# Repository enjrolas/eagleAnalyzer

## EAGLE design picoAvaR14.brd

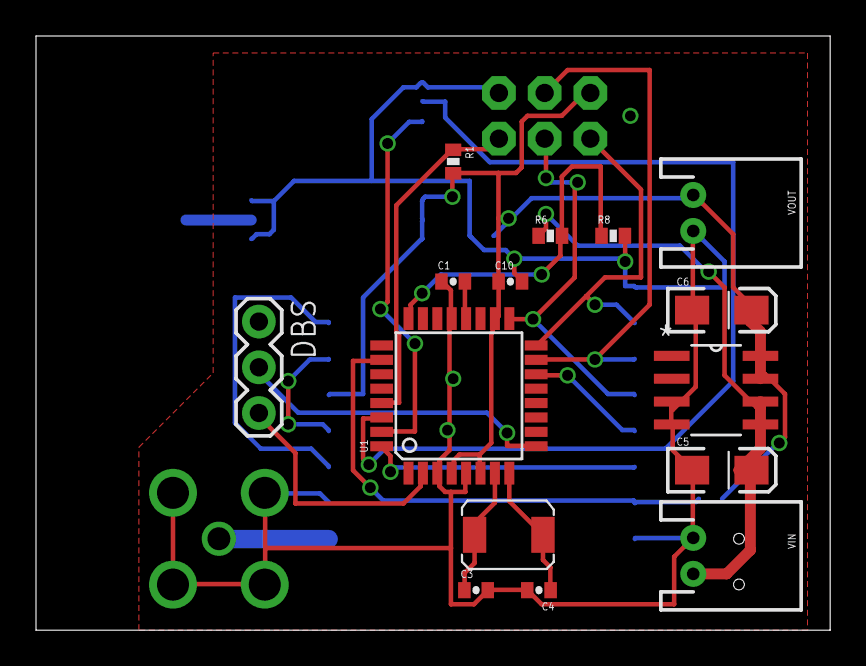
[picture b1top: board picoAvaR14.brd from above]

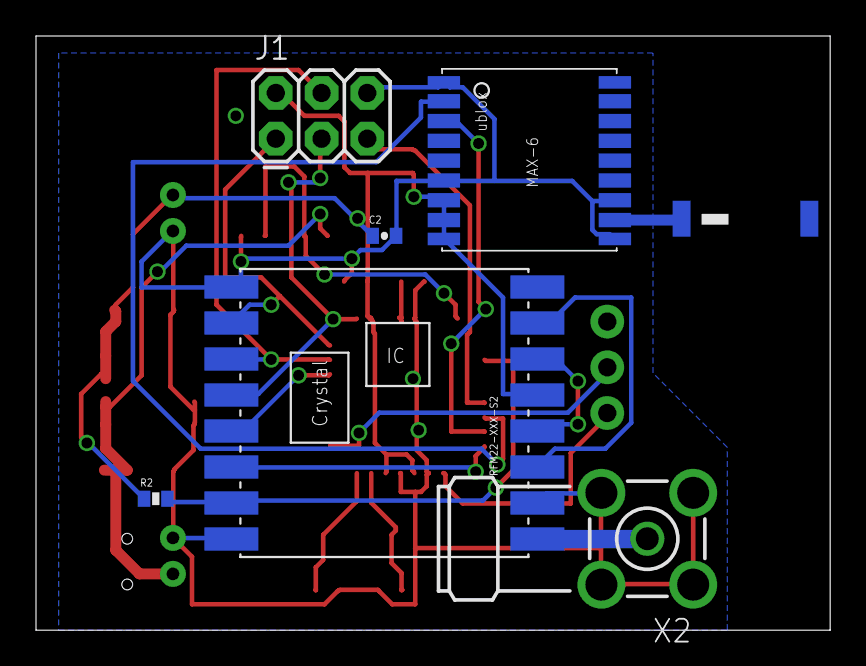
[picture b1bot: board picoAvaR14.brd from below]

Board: 2 copper layers, 44.1 x 33.0 mm, 24 parts (7 on the bottom side), 22 nets.

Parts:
C1, C2, C10: 0.1uF; 0402-CAP
C3, C4: 18pF; 0402-CAP
C5: EIA3216-KIT
C6: 4.7uF; EIA3216-KIT
DBS: 1X03
J1: AVR_SPI_PRG_6PTH; 2X3
JP1, JP2: STAND-OFF
R1, R2, R8: 10k; 0402-RES
R6: 100k; 0402-RES
RFM22-XXX-S2: RFM22; RFM22-XXX-S2
U1: ATMEGA328; TQFP32-08
U2: TPS76633D; SOIC127P600X175-8N
U$1: UBLOX_MAX-6
U$2: ABRACON_ABM3_CRYSTAL
U$3: JTI_ANTENNA-1575AT43A40
VIN: JST-2-PTH
VOUT: JST-2-PTH
X2: BU-SMA-H

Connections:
AREF: C1.2, U1.20
GND: C1.1, C2.2, C3.2, C4.2, C5.C, C6.C, C10.2, DBS.1, J1.6, R8.2, RFM22-XXX-S2.2, RFM22-XXX-S2.9, RFM22-XXX-S2.16, U1.3, U1.5, U1.21, U2.3, U2.4, U$1.1_GND, U$1.6_V_BCKP, U$1.10_GND, U$1.12_GND, VIN.1, VOUT.2, X2.2, X2.3, X2.4, X2.5
MISO: J1.1, RFM22-XXX-S2.10, U1.16
MOSI: J1.4, RFM22-XXX-S2.11, U1.15
unnamed: RFM22-XXX-S2.1, X2.1
unnamed: U$1.11_RF_IN, U$3.FEED
unnamed: RFM22-XXX-S2.3, RFM22-XXX-S2.7
unnamed: RFM22-XXX-S2.4, RFM22-XXX-S2.6
unnamed: C3.1, U1.7, U$2.P$2
unnamed: C4.1, U1.8, U$2.P$1
NSS_RX: DBS.2, U1.9
NSS_TX: DBS.3, U1.2
RESET: J1.5, R1.1, U1.29
RFM22_NIRQ: RFM22-XXX-S2.14, U1.32
RFM22_NSEL: RFM22-XXX-S2.13, U1.14
RFM22_SDN: R2.2, RFM22-XXX-S2.15, U1.26
SCK: J1.3, RFM22-XXX-S2.12, U1.17
UBLOX_RXD: U1.31, U$1.3_RXD1
UBLOX_TXD: U1.30, U$1.2_TXD1
VBATT: C5.A, R6.1, U2.5, U2.6, VIN.2
VBATTADC: R6.2, R8.1, U1.24
VCC: C2.1, C6.A, C10.1, J1.2, R1.2, R2.1, RFM22-XXX-S2.5, U1.4, U1.6, U1.18, U2.7, U2.8, U$1.7_VCC_IO, U$1.8_VCC, U$1.9_V_RESET, VOUT.1

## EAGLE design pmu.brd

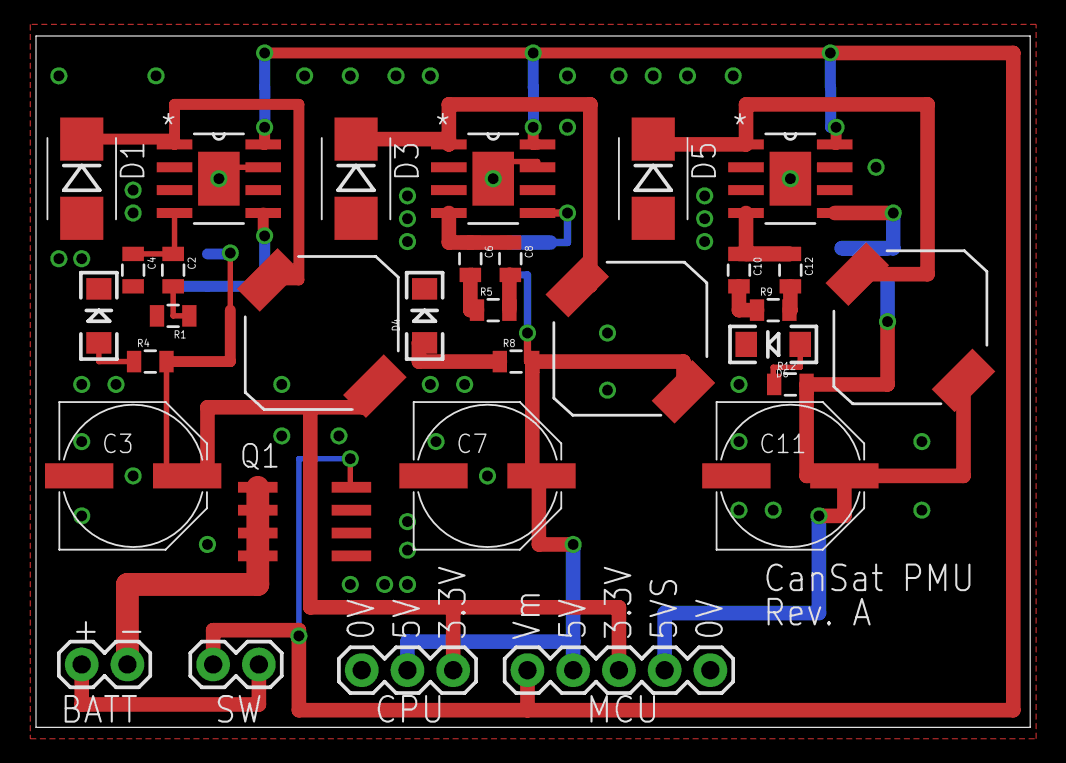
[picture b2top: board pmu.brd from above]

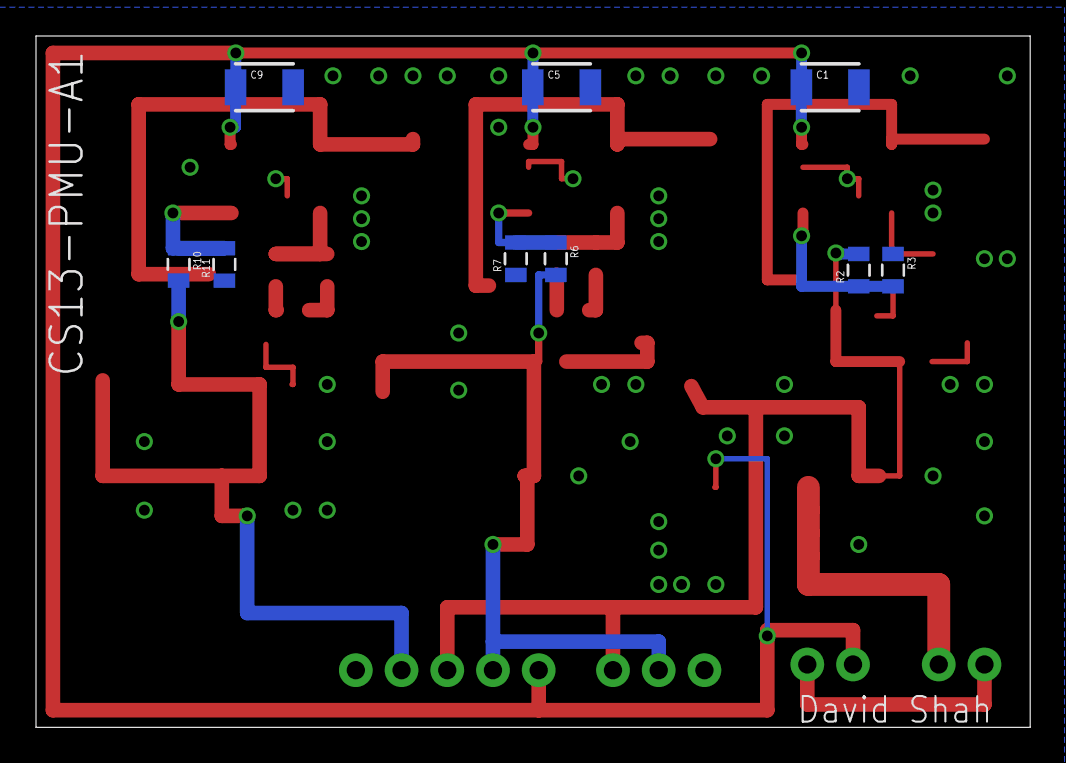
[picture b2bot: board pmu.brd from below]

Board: 2 copper layers, 55.2 x 38.4 mm, 41 parts (9 on the bottom side), 22 nets.

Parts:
BATT: 1X02
C1, C5, C9: 10u; 1210
C2, C6, C10: 22n; 0805
C3, C7, C11: 330u; PANASONIC_E
C4, C8, C12: 220p; 0805
CPU_PWR: 1X03
D1, D3, D5: SMB-DIODE
D2, D4, D6: GREEN; LED-1206
L1, L2, L3: 15uH; IND_ELL8TP
MCU_PWR: 1X05
PSW: 1X02
Q1: SO-08
R1, R5, R9: 4k7; 0805
R2: 5.6k; 0805
R3: 3.3k; 0805
R4, R8, R12: 330; 0805
R6, R10: 8.2k; 0805
R7, R11: 2.7k; 0805
U1, U2, U3: L5973D; SOP127P600X170-9N

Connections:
3.3V: C3.+, CPU_PWR.3, L1.1, MCU_PWR.3, R2.2, R4.2
5V: C7.+, CPU_PWR.2, L2.1, MCU_PWR.4, R6.2, R8.2
5VS: C11.+, L3.1, MCU_PWR.2, R10.2, R12.2
GND: C1.2, C3.-, C4.2, C5.2, C7.-, C8.2, C9.2, C11.-, C12.2, CPU_PWR.1, D1.A, D2.C, D3.A, D4.C, D5.A, D6.C, MCU_PWR.1, Q1.1, Q1.2, Q1.3, R1.2, R3.1, R5.2, R7.1, R9.2, R11.1, U1.3, U1.7, U1.9, U2.3, U2.7, U2.9, U3.3, U3.7, U3.9
unnamed: C2.1, C4.1, U1.4
unnamed: C2.2, R1.1
unnamed: D1.C, L1.2, U1.1
unnamed: BATT.2, Q1.5, Q1.6, Q1.7, Q1.8
unnamed: R2.1, R3.2, U1.5
unnamed: D2.A, R4.1
unnamed: C10.1, C12.1, U3.4
unnamed: C6.1, C8.1, U2.4
unnamed: C6.2, R5.1
unnamed: D3.C, L2.2, U2.1
unnamed: R6.1, R7.2, U2.5
unnamed: D4.A, R8.1
unnamed: C10.2, R9.1
unnamed: D5.C, L3.2, U3.1
unnamed: R10.1, R11.2, U3.5
unnamed: D6.A, R12.1
unnamed: BATT.1, PSW.2
V_BATT: C1.1, C5.1, C9.1, MCU_PWR.5, PSW.1, Q1.4, U1.8, U2.8, U3.8

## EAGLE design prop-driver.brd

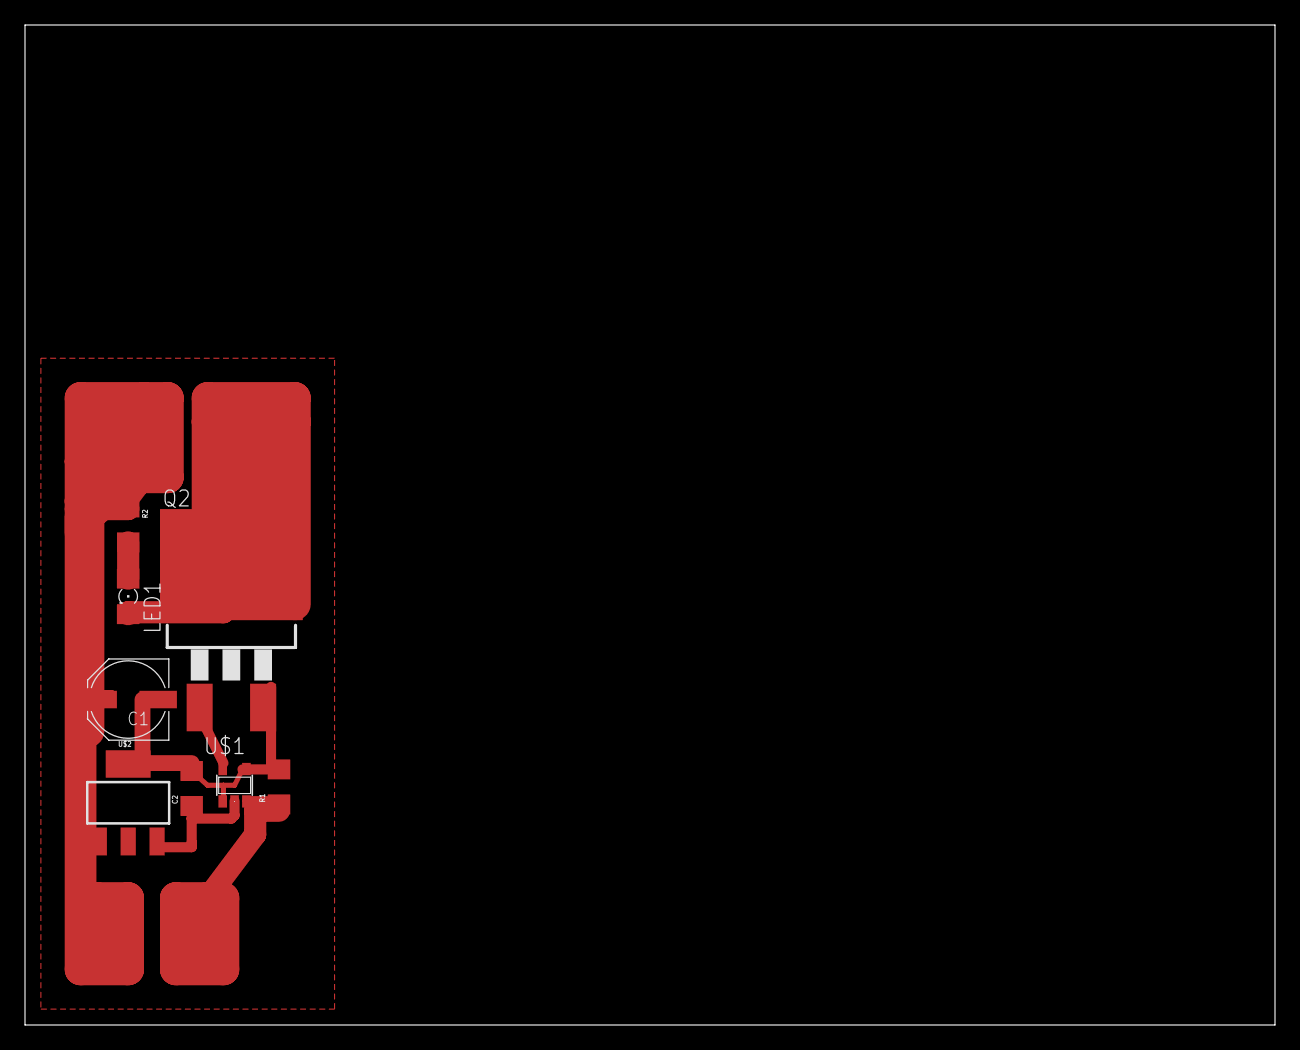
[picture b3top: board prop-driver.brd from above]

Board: 2 copper layers, 100.0 x 80.0 mm, 8 parts (0 on the bottom side), 7 nets.

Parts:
C1: PANASONIC_D
C2: 1206
LED1: FKIT-LED-1206
Q2: IRF3704S; D2PACK
R1, R2: 1206
U$1: MCP1402; SOT23-5
U$2: V_REG_MIC2920; SOT223

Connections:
+5V: C2.1, U$1.2, U$2.3
GND: C1.-, C2.2, Q2.3, R1.2, U$1.1, U$1.4, U$2.2
unnamed: Q2.1, U$1.5
unnamed: R1.1, U$1.3
unnamed: LED1.C, Q2.2
unnamed: LED1.A, R2.2
VDD: C1.+, R2.1, U$2.1

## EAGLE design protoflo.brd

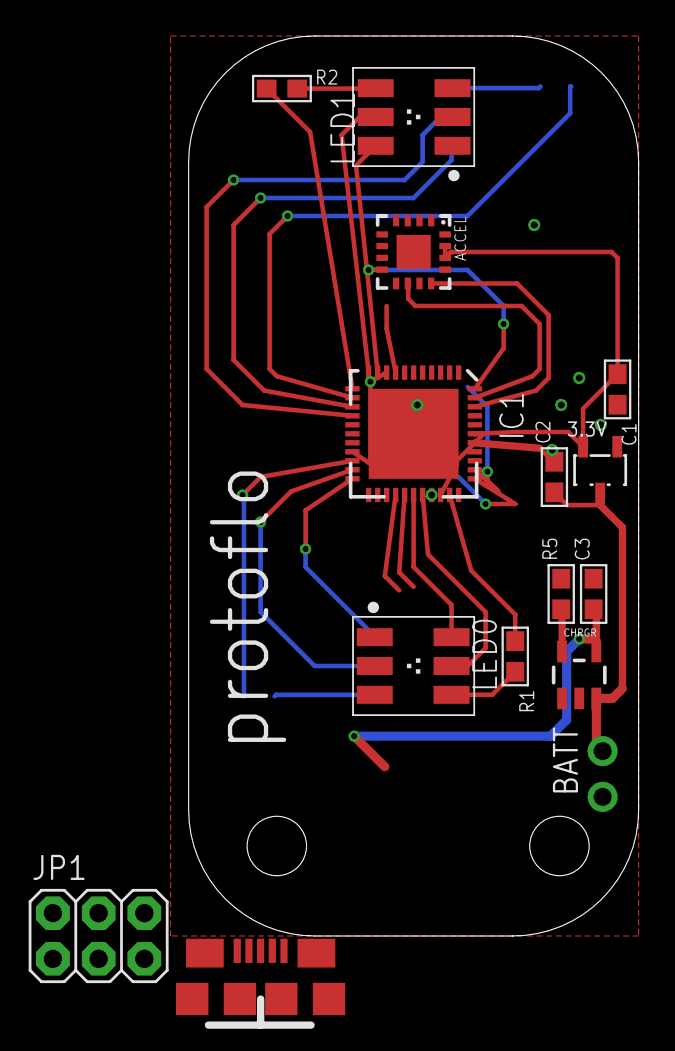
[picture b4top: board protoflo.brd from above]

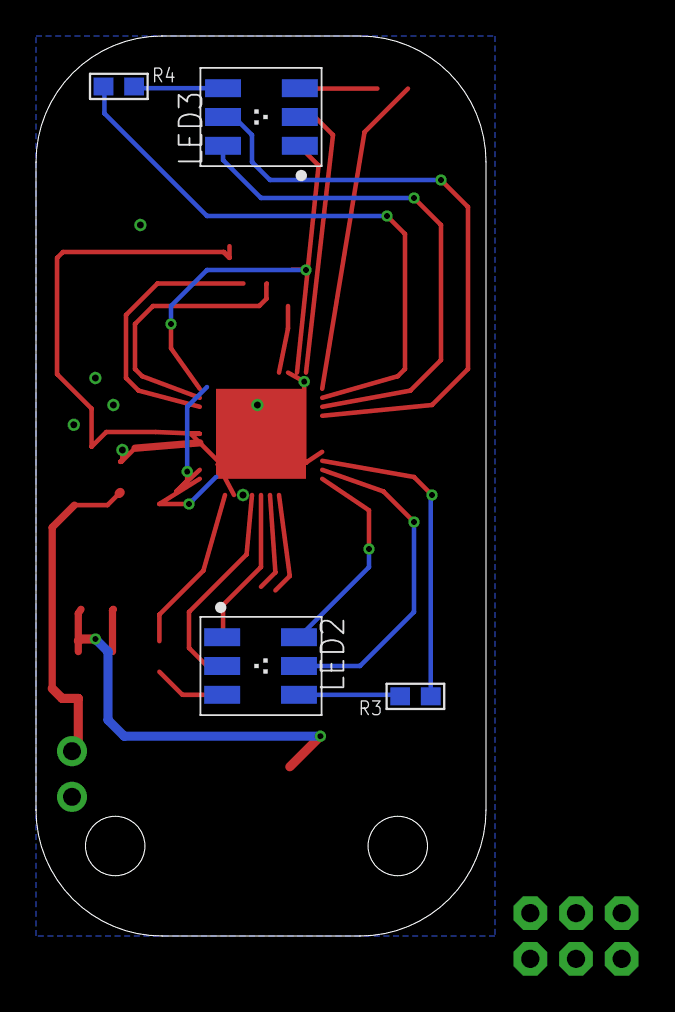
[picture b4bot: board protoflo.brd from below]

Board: 2 copper layers, 25.0 x 50.0 mm, 21 parts (4 on the bottom side), 28 nets.

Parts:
3.3V: VREG; SOT23-3
ACCEL: LFCSP-16
BATT: 1X02_ROUND
C1: .1uF; 0603
C2: 1uF; 0603
C3: 4.7uF; 0603
CHRGR: MCP73831; SOT23-5
CN1: USB-MICROB
IC1: QFN-44
JP1: 2X03
LED0, LED1, LED2, LED3: RGBLED_PLCC6
R1, R2, R3, R4, R5: 0603
U$1, U$2: STAND-OFF

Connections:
3.3V: 3.3V.2, ACCEL.14, ACCEL.15, C1.1, IC1.9, IC1.19, IC1.31, IC1.39, JP1.2
5V: 3.3V.3, C3.1, CHRGR.4, CN1.P1
ACCEL-X: ACCEL.12, IC1.42
ACCEL-Y: ACCEL.10, IC1.43
ACCEL-Z: ACCEL.8, IC1.44
BATT: BATT.2, C2.1, CHRGR.3
D+: CN1.P3, IC1.27
D-: CN1.P2, IC1.26
GND: 3.3V.1, ACCEL.3, ACCEL.5, ACCEL.6, ACCEL.7, BATT.1, C1.2, C2.2, C3.2, CHRGR.2, CN1.P5, IC1.8, IC1.18, IC1.30, IC1.38, JP1.6, LED0.1, LED0.2, LED0.3, LED1.1, LED1.2, LED1.3, LED2.1, LED2.2, LED2.3, LED3.1, LED3.2, LED3.3, R5.2
LED0B: IC1.28, LED0.6
LED0G: IC1.29, LED0.5
LED0R: LED0.4, R1.2
LED0RR: IC1.32, R1.1
LED1B: IC1.10, LED1.6
LED1G: IC1.11, LED1.5
LED1R: LED1.4, R2.2
LED1RR: IC1.12, R2.1
LED2B: IC1.22, LED2.6
LED2G: IC1.21, LED2.5
LED2R: LED2.4, R3.2
LED2RR: IC1.20, R3.1
LED3B: IC1.14, LED3.6
LED3G: IC1.15, LED3.5
LED3R: LED3.4, R4.2
LED3RR: IC1.13, R4.1
unnamed: CHRGR.5, R5.1
PDI-CLK: IC1.35, JP1.5
PDI-DATA: IC1.34, JP1.1

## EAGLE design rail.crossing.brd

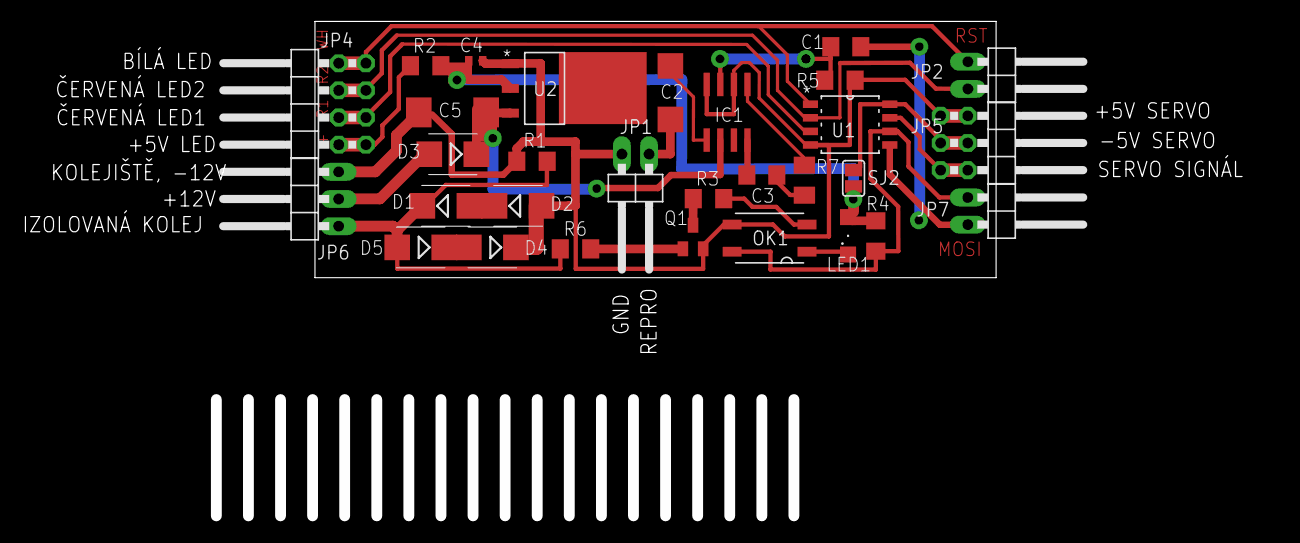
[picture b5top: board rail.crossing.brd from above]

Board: 2 copper layers, 63.7 x 24.0 mm, 30 parts (0 on the bottom side), 25 nets.

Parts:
C1: 100nF; C1206
C2: 100uF; SMC_C
C3: 10uF; C1206
C4: 1uF; C0402
C5: SMC_D
D1, D2, D3, D4, D5: M1; SMB
IC1: LM386M-1; SO08
JP1, JP2, JP7: 1X02/90
JP4: 2X04/90
JP5: 2X03/90
JP6: 1X03/90
LED1: KPT-3216SRD-PRV; SML1206
OK1: PC357N14; SMD4
Q1: BC847SMD; SOT23
R1: 2k2; R1206
R2, R3: 220; R1206
R4, R5: 10K; R1206
R6: 1K; R1206
R7: 1K; M1206
SJ2: SJ
U1: ATTINY85V-10SU; SOIC127P798X216-8N
U2: LM1117MP-5.0; SOT230P696X180-4N

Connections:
220: LED1.C, OK1.1
JP1: D3.C, D5.A, JP6.1, R1.1, R6.1
JP2: C4.2, D2.A, D4.C, IC1.2, IC1.4, JP1.2, JP5.1, JP5.2, JP6.3, OK1.3, Q1.2, R1.2, R5.2, U1.4, U2.1
unnamed: C2.-, JP1.1
unnamed: C3.1, R7.1
unnamed: C3.2, IC1.8
unnamed: D2.C, D3.A
unnamed: D4.A, D5.C
unnamed: Q1.1, R6.2
unnamed: Q1.3, R3.1
unnamed: C2.+, IC1.5
unnamed: OK1.2, R3.2
unnamed: JP5.5, JP5.6, U1.7
unnamed: C1.1, JP7.2, U1.5
unnamed: JP4.1, JP4.2, R2.1
unnamed: JP7.1, OK1.4, R4.1, U1.6
unnamed: JP5.3, JP5.4, LED1.A, R2.2, R4.2, SJ2.2, U1.8
unnamed: IC1.1, R7.2
unnamed: C1.2, IC1.3, R5.1
unnamed: C4.1, SJ2.1, U2.2
unnamed: D1.A, JP6.2
unnamed: C5.+, D1.C, IC1.6, U2.3
RED1: JP2.2, JP4.5, JP4.6, U1.2
RED2: JP4.3, JP4.4, U1.3
WHITE: JP2.1, JP4.7, JP4.8, U1.1

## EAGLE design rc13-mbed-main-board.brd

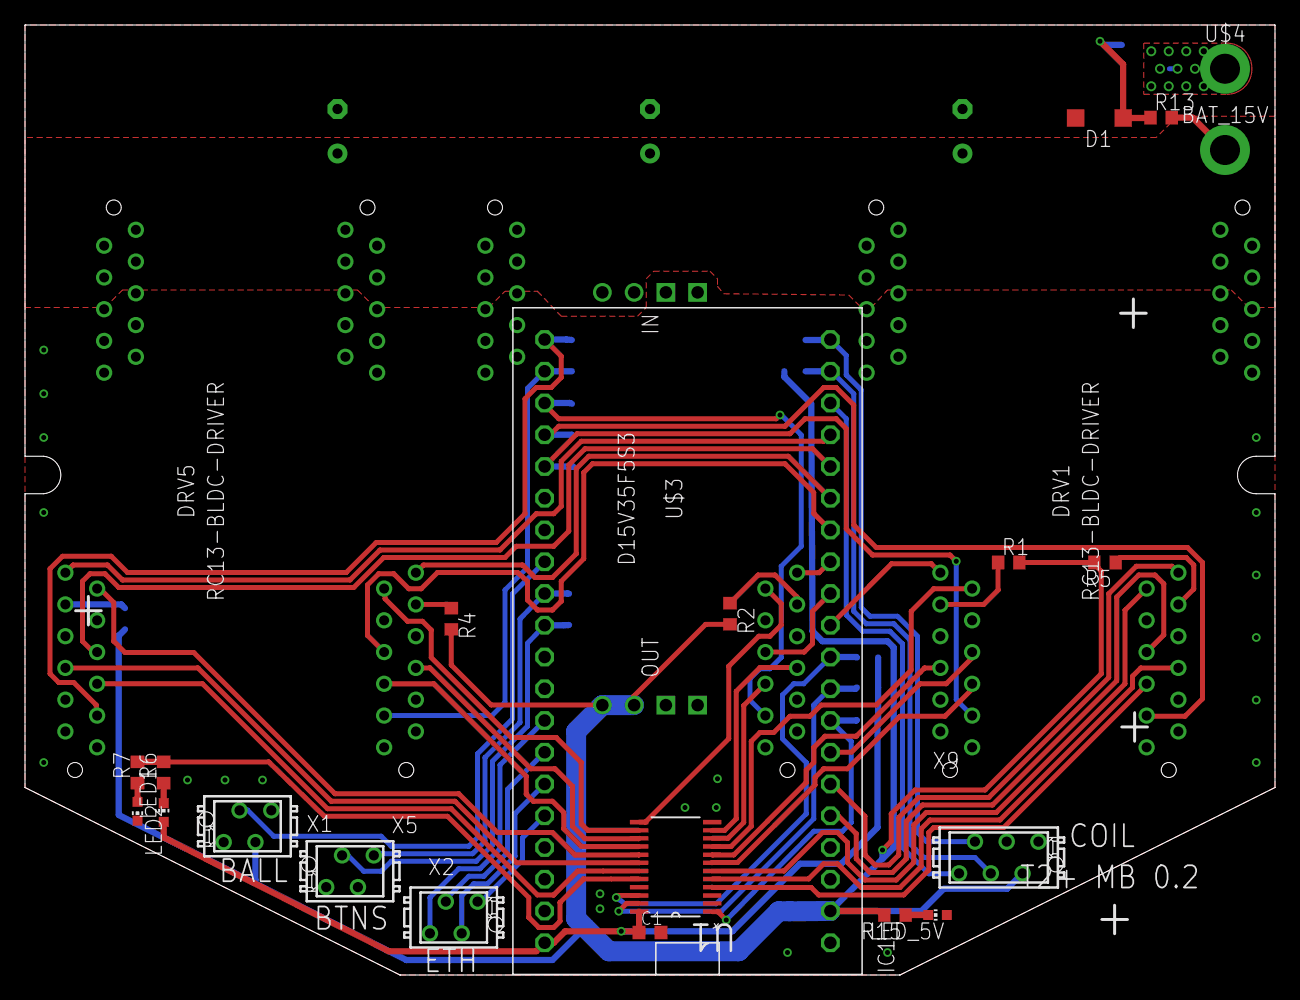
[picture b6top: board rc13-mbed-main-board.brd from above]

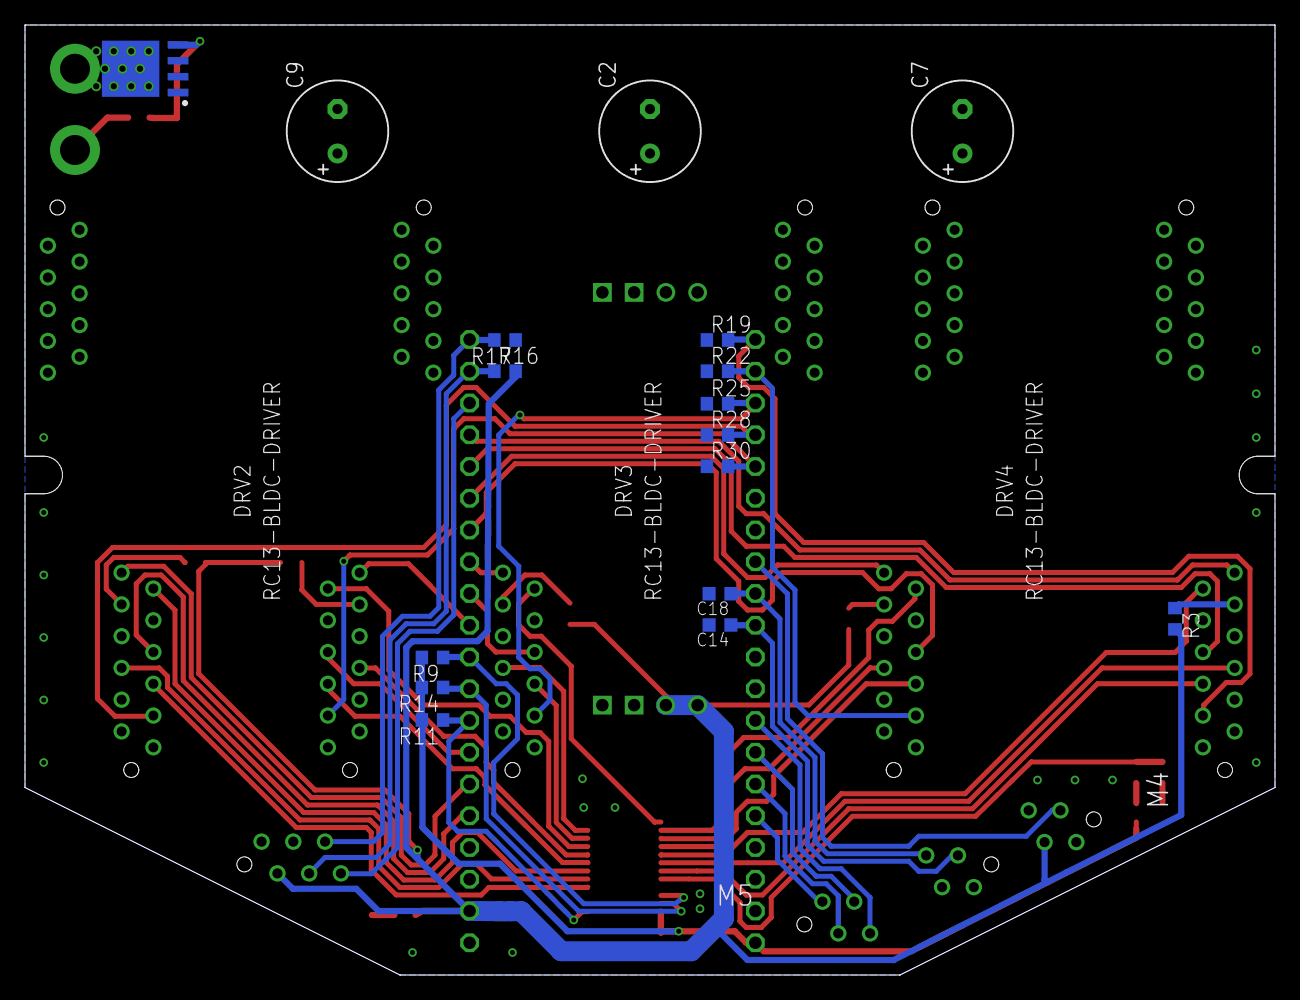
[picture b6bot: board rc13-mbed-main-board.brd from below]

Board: 2 copper layers, 100.0 x 76.0 mm, 44 parts (20 on the bottom side), 58 nets.

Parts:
BAT_15V: M01_PWR; PWR_HOLE
C1, C14, C18: 100nF; C0603K
C2, C7, C9: 470uF; E3,5-8
D1: 12V; SOD123
DRV1, DRV2, DRV3, DRV4, DRV5: RC13-BLDC-DRIVER
IC1: MBED_MICROCONTROLLER; DIL40_0.9
LED1, LED2: CHIP-LED0603
LED_5V: CHIP-LED0603
R1, R2, R3, R4, R5, R16, R17, R19, R22, R25, R28, R30: 10k; R0603
R6, R7, R9, R11, R14, R15: 2K2; R0603
R13: 100k; R0603
U1: PCA9555PW,118; SOP65P640X110-24N
U$2: MOSFET-N; TO127P600X120-5N
U$3: D15V35F5S3
U$4: M01_PWR; PWR_HOLE
X1: BALL_SENS; MICROMATCH-4
X2: ETH; MICROMATCH-4
X5: BTNS; MICROMATCH-4
X9: COIL; MICROMATCH-6

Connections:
+3V3: C1.1, IC1.40, LED1.A, R9.2, R11.2, R14.2, U1.24
+5V: IC1.2, R1.2, R2.2, R3.2, R4.2, R5.2, R15.2, R16.2, U$3.P$7, U$3.P$8, X1.3, X9.2
+15V: BAT_15V.P$1, C2.+, C7.+, C9.+, DRV1.PWR1, DRV1.PWR2, DRV1.PWR3, DRV1.PWR4, DRV1.PWR5, DRV2.PWR1, DRV2.PWR2, DRV2.PWR3, DRV2.PWR4, DRV2.PWR5, DRV3.PWR1, DRV3.PWR2, DRV3.PWR3, DRV3.PWR4, DRV3.PWR5, DRV4.PWR1, DRV4.PWR2, DRV4.PWR3, DRV4.PWR4, DRV4.PWR5, DRV5.PWR1, DRV5.PWR2, DRV5.PWR3, DRV5.PWR4, DRV5.PWR5, R13.2, U$3.EN, U$3.P$5
BALL: IC1.28, X1.2
BAT_GND: U$2.5, U$4.P$1
BRAKE1: DRV1.LOGIC6, U1.8
BRAKE2: DRV2.LOGIC6, U1.5
BRAKE3: DRV3.LOGIC6, U1.11
BRAKE4: DRV4.LOGIC6, U1.15
BRAKE5: DRV5.LOGIC6, U1.18
BTN1: C14.1, IC1.30, X5.2
BTN2: C18.1, IC1.29, X5.4
CHARGE: IC1.20, R17.2, X9.5
COAST1: DRV1.LOGIC11, U1.9
COAST2: DRV2.LOGIC11, U1.6
COAST3: DRV3.LOGIC11, U1.13
COAST4: DRV4.LOGIC11, U1.14
COAST5: DRV5.LOGIC11, U1.17
DIR1: DRV1.LOGIC5, U1.7
DIR2: DRV2.LOGIC5, U1.4
DIR3: DRV3.LOGIC5, U1.10
DIR4: DRV4.LOGIC5, U1.16
DIR5: DRV5.LOGIC5, U1.19
DIRO1: DRV1.LOGIC12, IC1.11
DIRO2: DRV2.LOGIC12, IC1.6
DIRO3: DRV3.LOGIC12, IC1.13
DIRO4: DRV4.LOGIC12, IC1.15
DIRO5: DRV5.LOGIC12, IC1.17
DONE: IC1.18, X9.6
GND: C1.2, C2.-, C7.-, C9.-, C14.2, C18.2, D1.A, DRV1.LOGIC1, DRV1.LOGIC2, DRV1.PWR6, DRV1.PWR7, DRV1.PWR8, DRV1.PWR9, DRV1.PWR10, DRV2.LOGIC1, DRV2.LOGIC2, DRV2.PWR6, DRV2.PWR7, DRV2.PWR8, DRV2.PWR9, DRV2.PWR10, DRV3.LOGIC1, DRV3.LOGIC2, DRV3.PWR6, DRV3.PWR7, DRV3.PWR8, DRV3.PWR9, DRV3.PWR10, DRV4.LOGIC1, DRV4.LOGIC2, DRV4.PWR6, DRV4.PWR7, DRV4.PWR8, DRV4.PWR9, DRV4.PWR10, DRV5.LOGIC1, DRV5.LOGIC2, DRV5.PWR6, DRV5.PWR7, DRV5.PWR8, DRV5.PWR9, DRV5.PWR10, IC1.1, LED2.C, LED_5V.A, R17.1, R19.1, R22.1, R25.1, R28.1, R30.1, U1.2, U1.3, U1.12, U1.21, U$2.1, U$2.2, U$2.3, U$3.P$1, U$3.P$2, U$3.P$3, U$3.P$4, X1.1, X5.1, X5.3, X9.1
INT: IC1.8, R11.1, U1.1
KICK: IC1.19, R16.1, X9.4
LED1: R6.2, R7.2, U1.20
unnamed: DRV1.LOGIC10, R1.1
unnamed: DRV2.LOGIC10, R5.1
unnamed: DRV4.LOGIC10, R4.1
unnamed: DRV5.LOGIC10, R3.1
unnamed: DRV3.LOGIC10, R2.1
unnamed: LED1.C, R6.1
unnamed: LED2.A, R7.1
unnamed: LED_5V.C, R15.1
unnamed: D1.C, R13.1, U$2.4
PWM1: DRV1.LOGIC3, IC1.25, R30.2
PWM2: DRV2.LOGIC3, IC1.24, R28.2
PWM3: DRV3.LOGIC3, IC1.23, R25.2
PWM4: DRV4.LOGIC3, IC1.22, R22.2
PWM5: DRV5.LOGIC3, IC1.21, R19.2
RD+: IC1.35, X2.2
RD-: IC1.36, X2.1
SCL: IC1.10, R9.1, U1.22
SDA: IC1.9, R14.1, U1.23
TACHO1: DRV1.LOGIC7, IC1.7
TACHO2: DRV2.LOGIC7, IC1.5
TACHO3: DRV3.LOGIC7, IC1.12
TACHO4: DRV4.LOGIC7, IC1.14
TACHO5: DRV5.LOGIC7, IC1.16
TD+: IC1.33, X2.4
TD-: IC1.34, X2.3

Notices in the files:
parts and their libraries:
SparkFun-Passives: Licensing: CC v3.0 Share-Alike You are welcome to use this library for commercial purposes.
